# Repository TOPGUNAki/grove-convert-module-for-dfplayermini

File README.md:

# Grove Convert Module for DFPlayer mini

DFPlayer mini Grove変換モジュール

## 特長
DFPlayer miniを差し込むことにより、ホストマイコンからGroveコネクタ経由でDFPlayer miniを制御できます。  
基板のスルーホールにスピーカーを直接つないだり、φ3.5mmステレオジャック経由で外部のスピーカーと接続できます。  
実装したスピーカーの音量が足りないなぁ…というときに、外部スピーカー接続に変更して音量を上げるといったこともできます。  
また、通信確認用のLEDも実装しています。

## デモ
### micro:bit

[micro:bit プログラム例](https://makecode.microbit.org/_3q2T52P9qFmp)

## 注意点
DFPlayer miniのピンソケットが若干狭いので、少し広げて接続してください。

## スペック
 - 基板サイズ(コネクタ込): 40 × 24 × 12mm  
 - VCC電圧：3.3V or 5V
 - TX/RXピン信号電圧：3.3V
 - ジャック端子：ステレオミニ φ3.5mm

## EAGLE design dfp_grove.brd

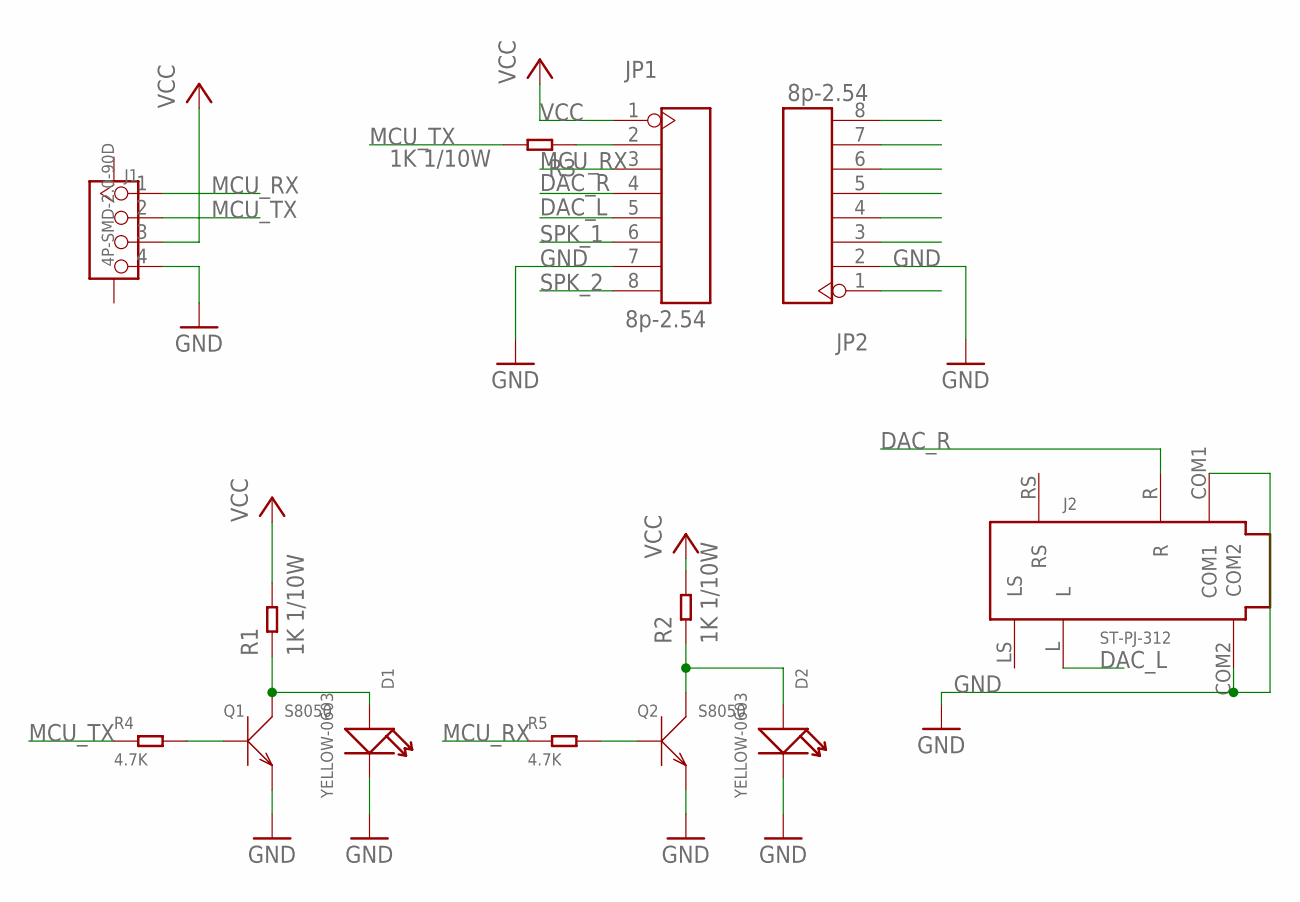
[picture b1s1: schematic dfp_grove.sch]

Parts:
D1, D2: YELLOW-0603; LED-0603
J1: 4P-SMD-2.0-90D; HW4-SMD-2.0-90D
J2: ST-PJ-312; AUDIO6P-SMD-3.5-14.0X6.4X5.0MM
JP1, JP2: 8p-2.54; H8-2.54
Q1, Q2: S8050; SOT-23
R1, R2, R3: 1K 1/10W; R0603
R4, R5: 4.7K; R0603

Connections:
DAC_L: J2.L, JP1.5
DAC_R: J2.R, JP1.4
GND: D1.-, D2.-, J1.4, J2.COM1, J2.COM2, JP1.7, JP2.2, Q1.2 (E), Q2.2 (E)
MCU_RX: J1.1, JP1.3, R5.1
MCU_TX: J1.2, R3.2, R4.1
unnamed: D2.+, Q2.3 (C), R2.1
unnamed: Q2.1 (B), R5.2
unnamed: Q1.1 (B), R4.2
unnamed: D1.+, Q1.3 (C), R1.1
RX: JP1.2, R3.1
SPK_1: JP1.6
SPK_2: JP1.8
VCC: J1.3, JP1.1, R1.2, R2.2

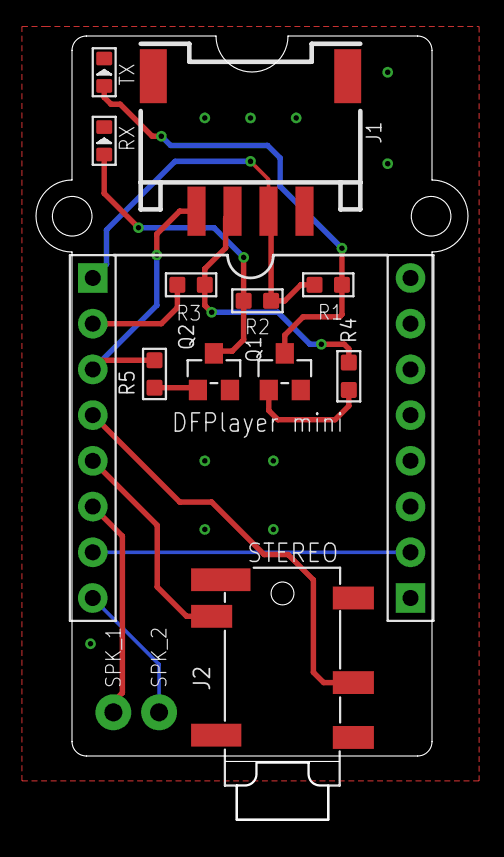
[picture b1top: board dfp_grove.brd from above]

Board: 2 copper layers, 24.0 x 43.5 mm, 13 parts (0 on the bottom side), 11 nets.

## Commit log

2021-03-18 first commit. this is v1.0.0
2021-03-18 Readmeを作成
2021-03-18 pcbフォルダに基板関連データを移動
2021-03-18 add pdf of pattern and schematics
2021-03-18 説明を追加
